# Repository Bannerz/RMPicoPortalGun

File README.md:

# RMPicoPortalGun
Repo for my Pico portal gun from Rick and Morty

Updated to use both cores of Pico for simultaneous loops, allowing for a constant animation of the plasma tube and operation of the dial/button at the same time.

Wiring:

I used blue tack because I'm lazy. Internet says it's non conductive so should be alright.

I used copper tape to create a cartridge like system so you can just slide the tray in and out for charging. Detachable wires also work (thats what I used in my first version, it was just annoying to stuff the wires in each time)

Inside the case, I placed copper tape, then soldered the wires onto it while it was inside. This was difficult, but doable. Good luck!

Get the micropython display driver here: https://github.com/smittytone/HT16K33-Python

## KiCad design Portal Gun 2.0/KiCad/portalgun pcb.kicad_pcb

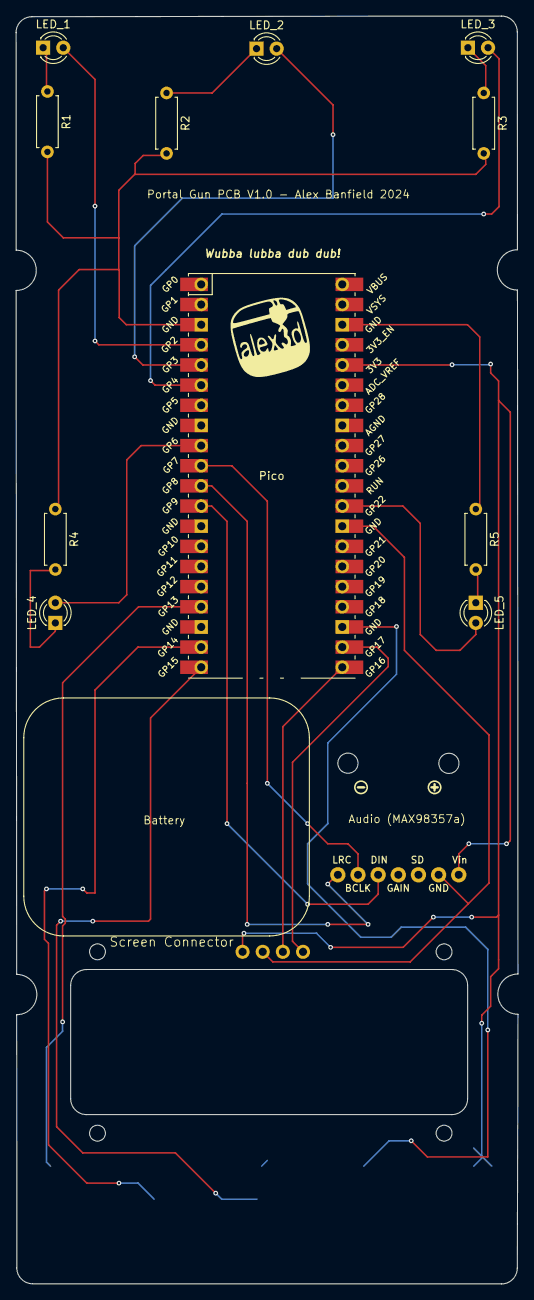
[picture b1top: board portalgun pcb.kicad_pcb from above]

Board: 2 copper layers, 63.3 x 159.8 mm, 17 parts (0 on the bottom side), 11 nets.

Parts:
@HOLE1, @HOLE2, @HOLE3: (no value)
JP1: 1X07_ROUND_76
LED_1, LED_2, LED_3, LED_4, LED_5: LED_D3.0mm
Pico: RPi_Pico_SMD_TH
R1: R1; R_Axial_DIN0207_L6.3mm_D2.5mm_P7.62mm_Horizontal
R2: R2; R_Axial_DIN0207_L6.3mm_D2.5mm_P7.62mm_Horizontal
R3: R3; R_Axial_DIN0207_L6.3mm_D2.5mm_P7.62mm_Horizontal
R4: R4; R_Axial_DIN0207_L6.3mm_D2.5mm_P7.62mm_Horizontal
R5: R5; R_Axial_DIN0207_L6.3mm_D2.5mm_P7.62mm_Horizontal
minus: SYMBOL_MINUS
plus: SYMBOL_PLUS

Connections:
BLCK: JP1.6, Pico.10
DIN: JP1.5, Pico.12
LED_1: LED_1.2, Pico.4
LED_2: LED_2.2, Pico.5
LED_3: LED_3.2, Pico.6
LED_4: LED_4.2, Pico.9
LED_5: LED_5.2, Pico.29
LED_GND: LED_1.1, LED_2.1, LED_3.1, LED_4.1, LED_5.1, Pico.3, Pico.38, R1.1, R1.2, R2.1, R2.2, R3.1, R3.2, R4.1, R4.2, R5.1, R5.2
LRC: JP1.7, Pico.11
PAD_5: JP1.1, Pico.36
SCRNAUDI_GND: JP1.2, Pico.28

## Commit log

2023-10-11 Update main.py
    Added multithreading so animation can play on top LEDs while still allowing dial to be usable.
    Changed the front LEDs to be off until button clicked and plays a little light show before turning off again
2024-03-20 Portal Gun Version 2
    This is the new version built in Circuitpython to take advantage of Adafruits amazing libraries. This version adds sound and is written for the circuit board I designed (also included)
